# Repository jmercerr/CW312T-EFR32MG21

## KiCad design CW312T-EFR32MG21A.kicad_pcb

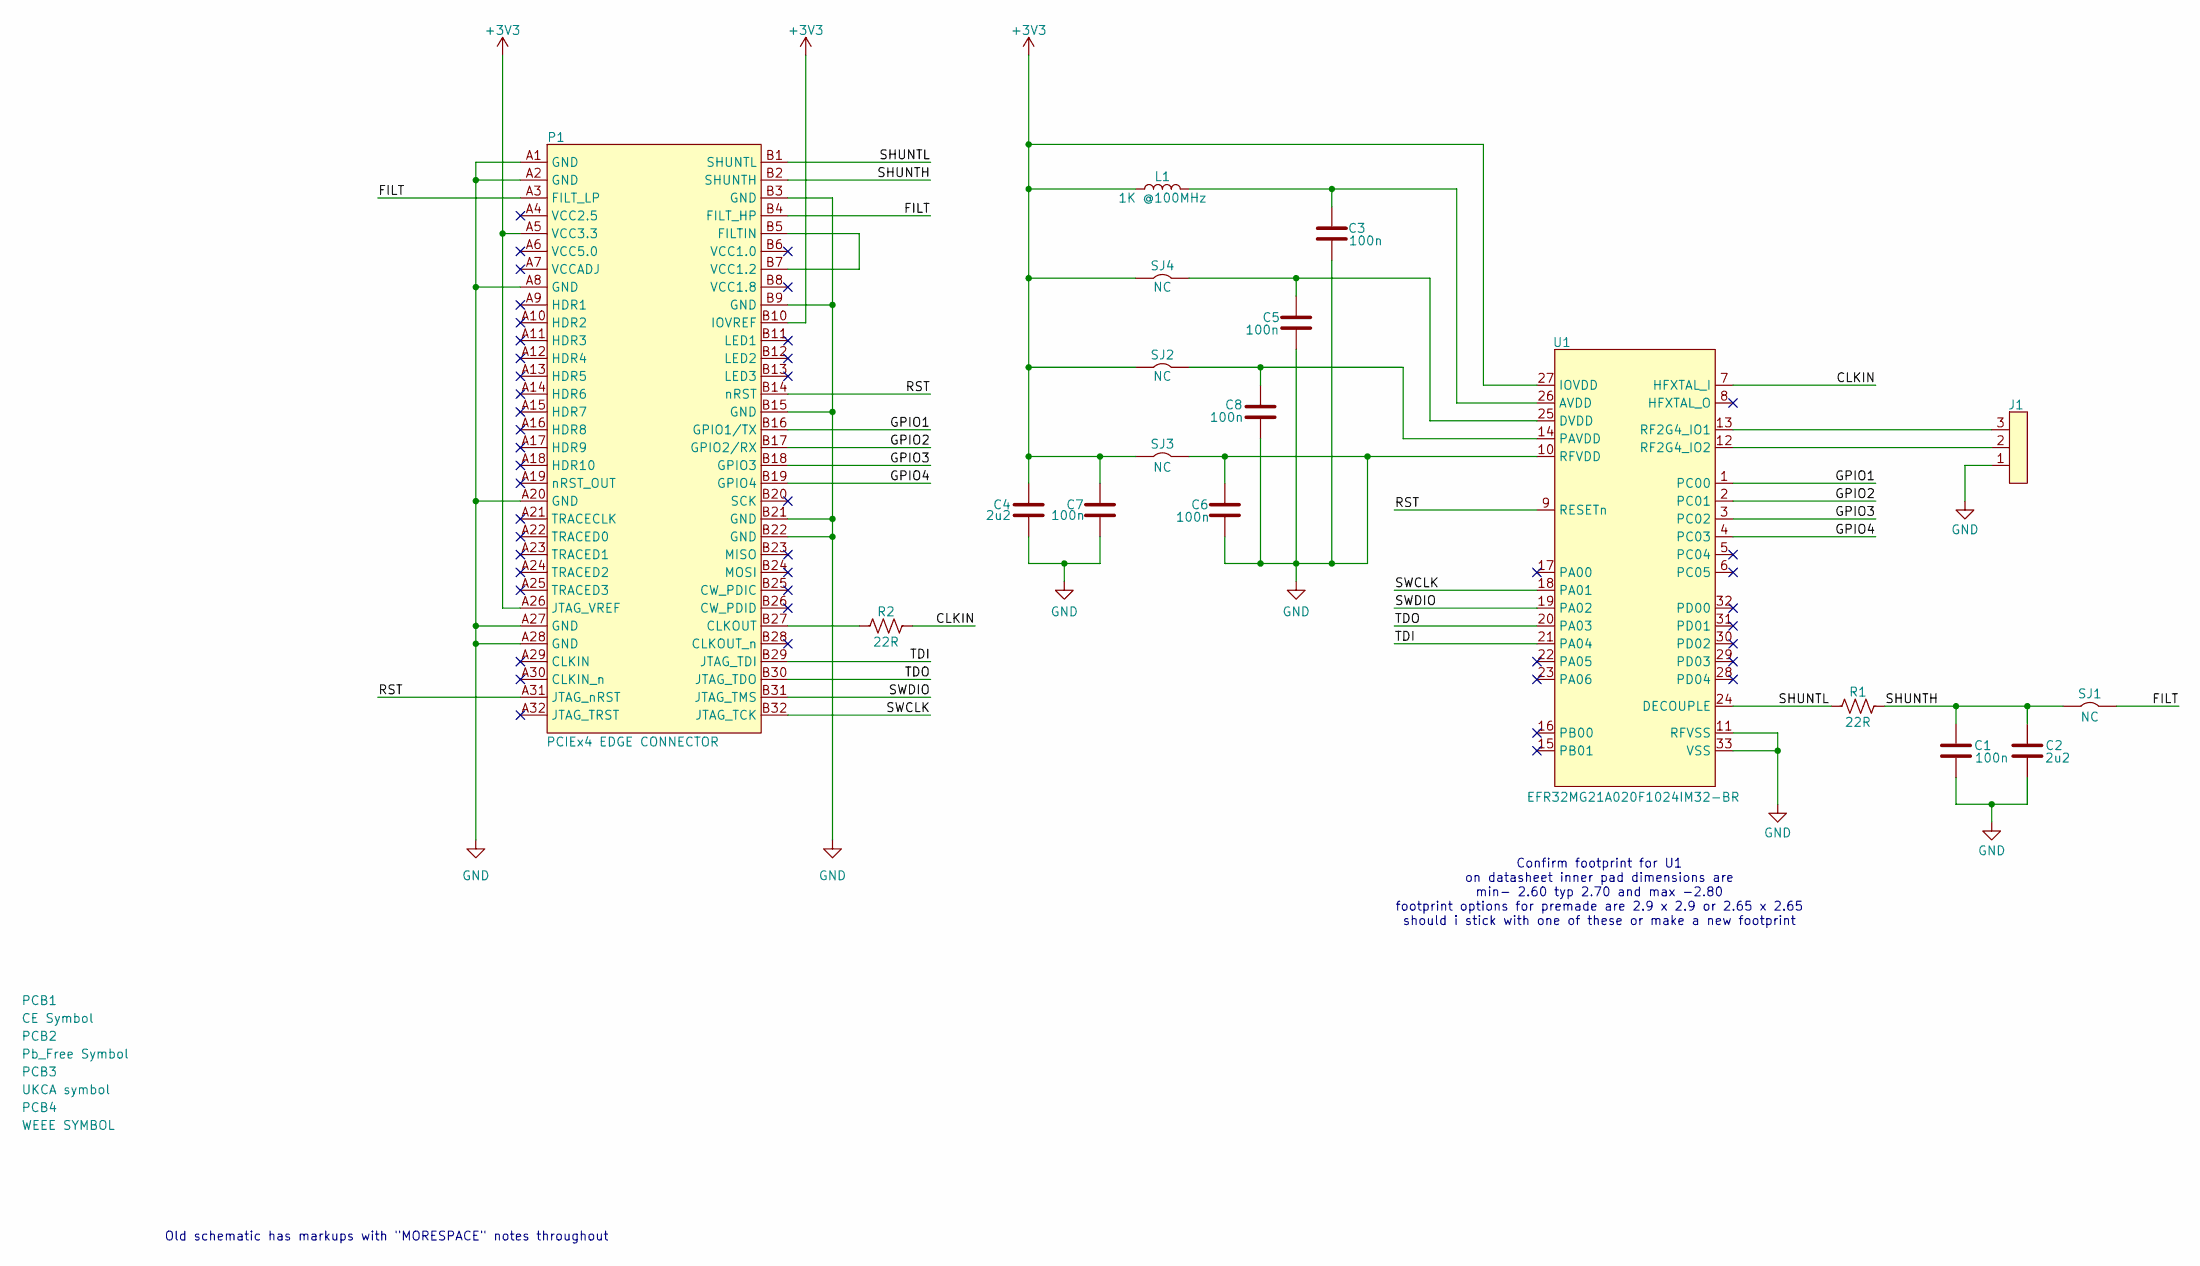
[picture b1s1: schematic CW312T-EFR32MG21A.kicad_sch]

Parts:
C1, C3, C5, C6, C7, C8: CAP_100n_10V_0603; C_0603_1608Metric; Manufacturer Part Number CC0603KRX7R6BB104
C2, C4: CAP_2u2_10V_0603; C_0603_1608Metric; Manufacturer Part Number CC0603KPX7R6BB225
J1: 1x3 straight header pins; PinHeader_1x03_P2.54mm_Vertical; Manufacturer Part Number 61300311121
L1: IND_1K_0603; L_0603_1608Metric; Manufacturer Part Number FBMH1608HM102-T
P1: PCIEx4 EDGE CONNECTOR; CW312_Template
PCB1: CE Symbol; CE-Logo_8.5x6mm_SilkScreen
PCB2: Pb_Free Symbol; Pb_Free_8.0x8.0mm_SilkScreen
PCB3: UKCA symbol; UKCA-Logo_8x8mm_SilkScreen
PCB4: WEEE SYMBOL; WEEE-Logo_5.6x8mm_SilkScreen
R1, R2: RES_22R_0603; R_0603_1608Metric; Manufacturer Part Number RC0603FR-0722RL
SJ1, SJ2, SJ3, SJ4: SolderJumper-2_P1.3mm_Bridged2Bar_Pad1.0x1.5mm
U1: EFR32MG21A020F1024IM32-BR; QFN-32-1EP_4x4mm_P0.4mm_EP2.9x2.9mm; Manufacturer Part Number EFR32MG21A020F1024IM32-BR

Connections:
+3V3: C4.2, C7.2, L1.1, P1.A5 (VCC3.3), P1.A26 (JTAG_VREF), P1.B10 (IOVREF), SJ2.2, SJ3.2, SJ4.2, U1.27 (IOVDD)
/CLKIN: R2.2, U1.7 (HFXTAL_I)
/FILT: P1.A3 (FILT_LP), P1.B4 (FILT_HP), SJ1.1
/GPIO1: P1.B16 (GPIO1/TX), U1.1 (PC00)
/GPIO2: P1.B17 (GPIO2/RX), U1.2 (PC01)
/GPIO3: P1.B18 (GPIO3), U1.3 (PC02)
/GPIO4: P1.B19 (GPIO4), U1.4 (PC03)
/RST: P1.A31 (JTAG_nRST), P1.B14 (nRST), U1.9 (RESETn)
/SHUNTH: C1.2, C2.2, P1.B2 (SHUNTH), R1.2, SJ1.2
/SHUNTL: P1.B1 (SHUNTL), R1.1, U1.24 (DECOUPLE)
/SWCLK: P1.B32 (JTAG_TCK), U1.18 (PA01)
/SWDIO: P1.B31 (JTAG_TMS), U1.19 (PA02)
/TDI: P1.B29 (JTAG_TDI), U1.21 (PA04)
/TDO: P1.B30 (JTAG_TDO), U1.20 (PA03)
GND: C1.1, C2.1, C3.1, C4.1, C5.1, C6.1, C6.2, C7.1, C8.1, J1.1, P1.A1 (GND), P1.A2 (GND), P1.A8 (GND), P1.A20 (GND), P1.A27 (GND), P1.A28 (GND), P1.B3 (GND), P1.B9 (GND), P1.B15 (GND), P1.B21 (GND), P1.B22 (GND), SJ3.1, U1.10 (RFVDD), U1.11 (RFVSS), U1.33 (VSS)
unnamed: P1.B27 (CLKOUT), R2.1
unnamed: P1.B5 (FILTIN), P1.B7 (VCC1.2)
unnamed: C3.2, L1.2, U1.26 (AVDD)
unnamed: C5.2, SJ4.1, U1.25 (DVDD)
unnamed: C8.2, SJ2.1, U1.14 (PAVDD)
unnamed: J1.3, U1.13 (RF2G4_IO1)
unnamed: J1.2, U1.12 (RF2G4_IO2)

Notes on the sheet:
Old schematic has markups with "MORESPACE" notes throughout
Confirm footprint for U1 on datasheet inner pad dimensions are min- 2.60 typ 2.70 and max -2.80 footprint options for premade are 2.9 x 2.9 or 2.65 x 2.65 should i stick with one of these or make a new footprint

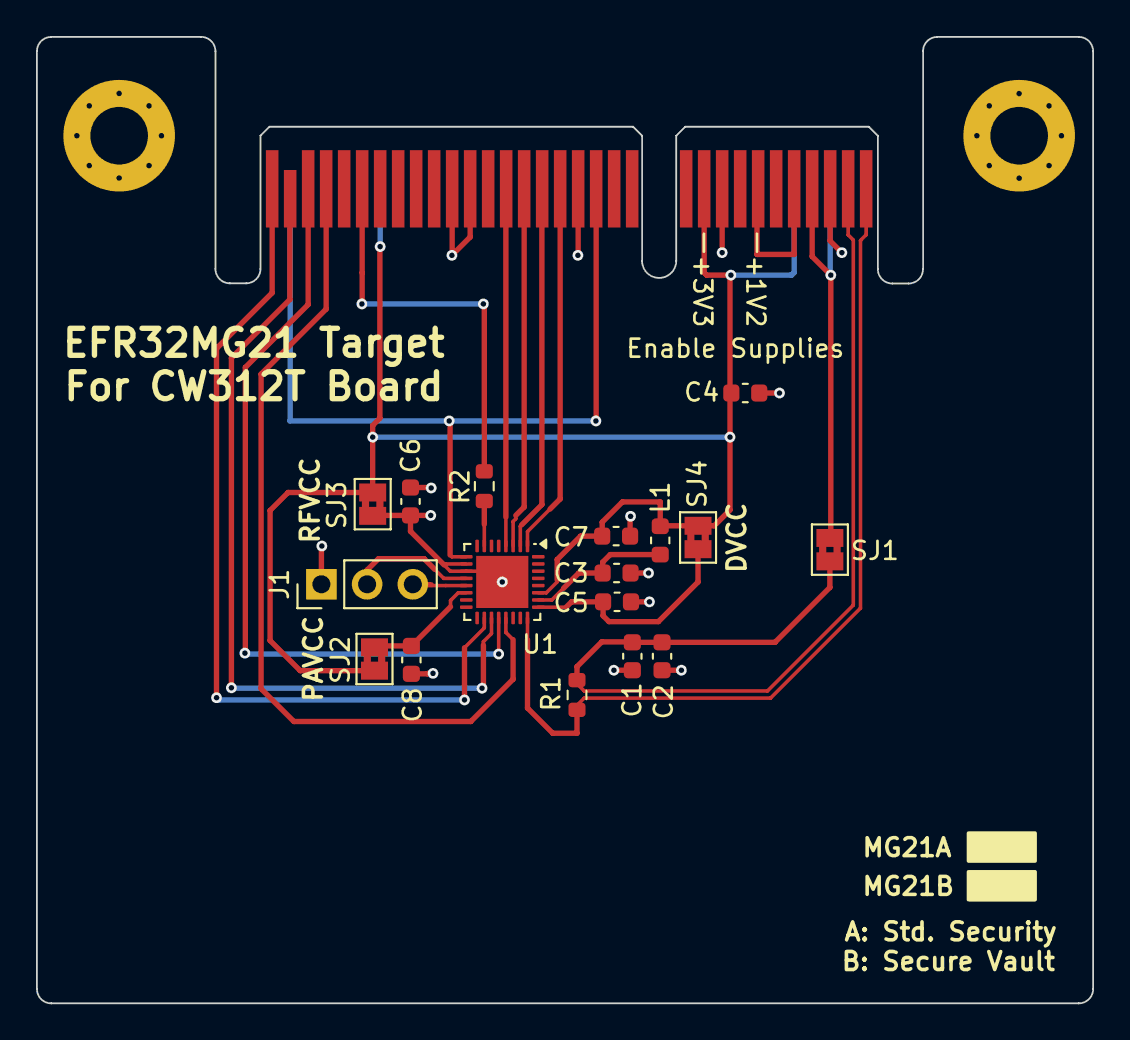
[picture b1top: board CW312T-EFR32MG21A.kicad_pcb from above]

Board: 2 copper layers, 58.7 x 53.7 mm, 22 parts (0 on the bottom side), 22 nets.

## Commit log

2024-11-29 first draft - ready for review
2024-12-04 updated schematic to fix power, updated pcb and production files - ready for review
2024-12-04 added comment about footprint
2024-12-04 updated silkscreen and production files
2024-12-19 updated 3 pin header to fix footprint
2024-12-19 updated schematic and pcb after library reorganization
